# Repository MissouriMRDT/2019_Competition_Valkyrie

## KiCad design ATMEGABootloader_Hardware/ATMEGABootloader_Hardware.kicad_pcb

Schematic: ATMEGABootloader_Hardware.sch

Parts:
A1: Arduino_UNO_R3
C1, C2: 20pF; C_0603_1608Metric_Pad1.05x0.95mm_HandSolder
JP1, JP2, JP3: Jumper; PinHeader_1x02_P2.54mm_Vertical
R1: 10k; R_0603_1608Metric_Pad1.05x0.95mm_HandSolder
U1: ATmega328-PU; DIP-28_W7.62mm
Y1: 16MHz; Crystal_HC49-U_Vertical

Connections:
+5V: A1.5, JP2.2, U1.7, U1.20
GND: A1.6, A1.7, A1.29, C1.1, C2.1, U1.8, U1.22
unnamed: C1.2, JP3.2, Y1.1
unnamed: C2.2, U1.10, Y1.2
unnamed: JP1.1, U1.2
unnamed: JP2.1, R1.1
unnamed: JP3.1, U1.9
P17: A1.26, U1.17
P18: A1.27, U1.18
P19: A1.28, U1.19
Rst: A1.25, R1.2, U1.1
Rx: A1.15, JP1.2
Tx: A1.16, U1.3

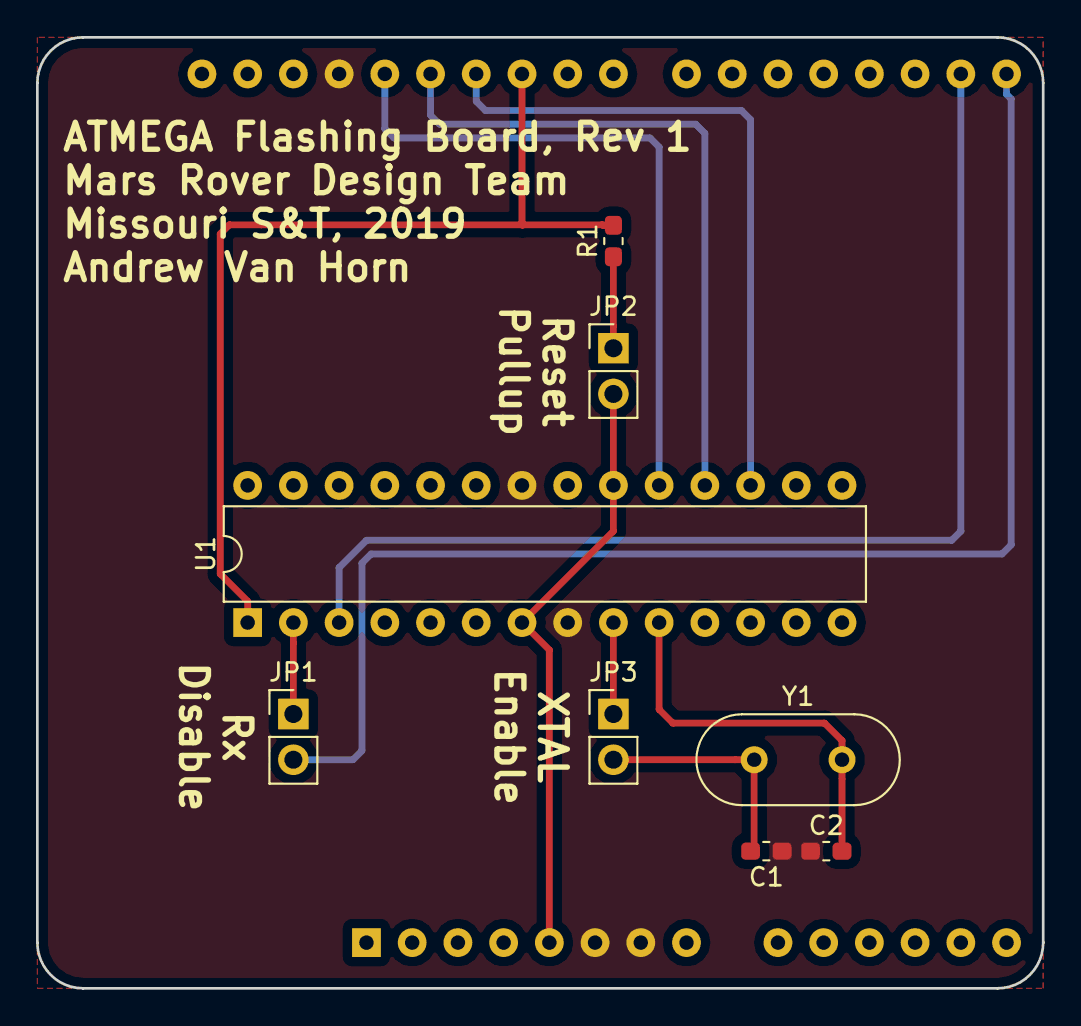
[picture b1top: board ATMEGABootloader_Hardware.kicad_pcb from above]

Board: 2 copper layers, 55.9 x 52.8 mm, 9 parts (1 on the bottom side), 13 nets.

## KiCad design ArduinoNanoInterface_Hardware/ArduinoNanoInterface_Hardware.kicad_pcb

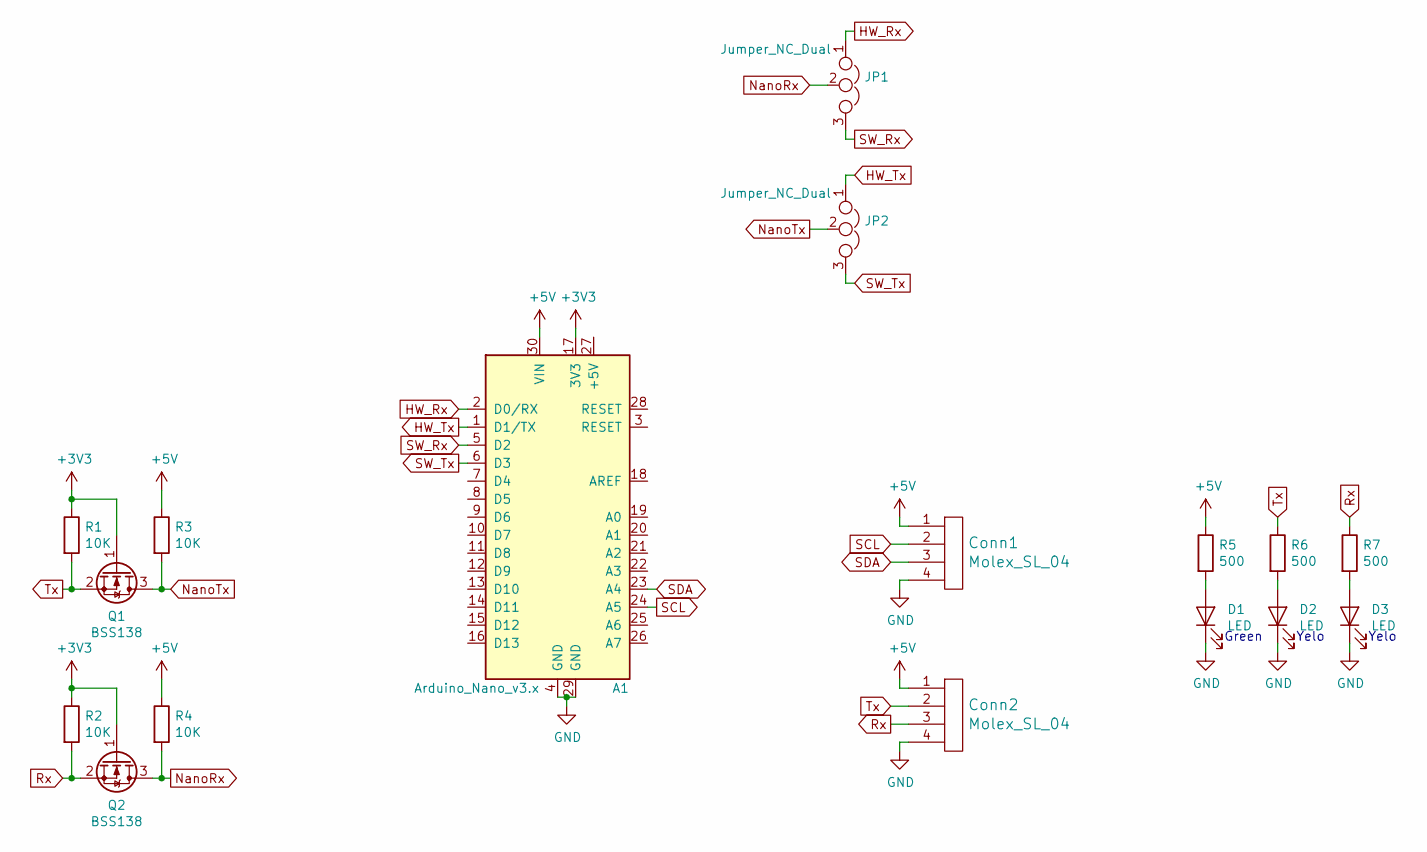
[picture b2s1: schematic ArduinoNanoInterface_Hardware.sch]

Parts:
A1: Arduino_Nano_v3.x; Arduino_Nano
Conn1, Conn2: Molex_SL_04; MOLEX_SL_04_Horizontal
D1, D2, D3: LED; LED_0603_1608Metric_Pad1.05x0.95mm_HandSolder
JP1, JP2: Jumper_NC_Dual; PinSocket_1x03_P2.54mm_Vertical
Q1, Q2: BSS138; SOT-23
R1, R2, R3, R4: 10K; R_0603_1608Metric_Pad1.05x0.95mm_HandSolder
R5, R6, R7: 500; R_0603_1608Metric_Pad1.05x0.95mm_HandSolder

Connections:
+3V3: A1.17 (3V3), Q1.1 (G), Q2.1 (G), R1.1, R2.1
+5V: A1.30 (VIN), Conn1.1, Conn2.1, R3.1, R4.1, R5.1
GND: A1.4 (GND), A1.29 (GND), Conn1.4, Conn2.4, D1.1 (K), D2.1 (K), D3.1 (K)
HW_Rx: A1.2 (D0/RX), JP1.1
HW_Tx: A1.1 (D1/TX), JP2.1
NanoRx: JP1.2, Q2.3 (D), R4.2
NanoTx: JP2.2, Q1.3 (D), R3.2
unnamed: D1.2 (A), R5.2
unnamed: D2.2 (A), R6.2
unnamed: D3.2 (A), R7.2
Rx: Conn2.3, Q2.2 (S), R2.2, R7.1
SCL: A1.24 (A5), Conn1.2
SDA: A1.23 (A4), Conn1.3
SW_Rx: A1.5 (D2), JP1.3
SW_Tx: A1.6 (D3), JP2.3
Tx: Conn2.2, Q1.2 (S), R1.2, R6.1

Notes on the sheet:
Green
Yelo

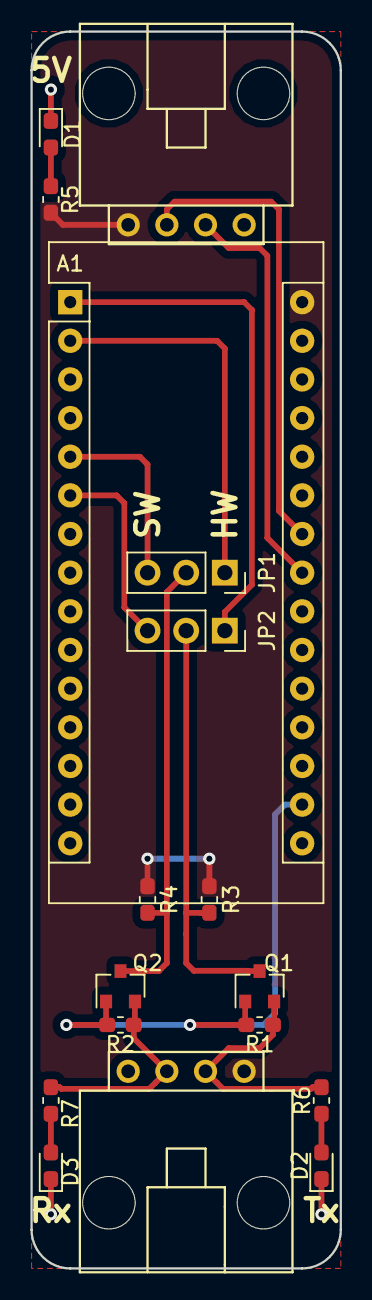
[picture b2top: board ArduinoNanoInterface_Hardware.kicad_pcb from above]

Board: 2 copper layers, 20.3 x 81.3 mm, 17 parts (0 on the bottom side), 16 nets.

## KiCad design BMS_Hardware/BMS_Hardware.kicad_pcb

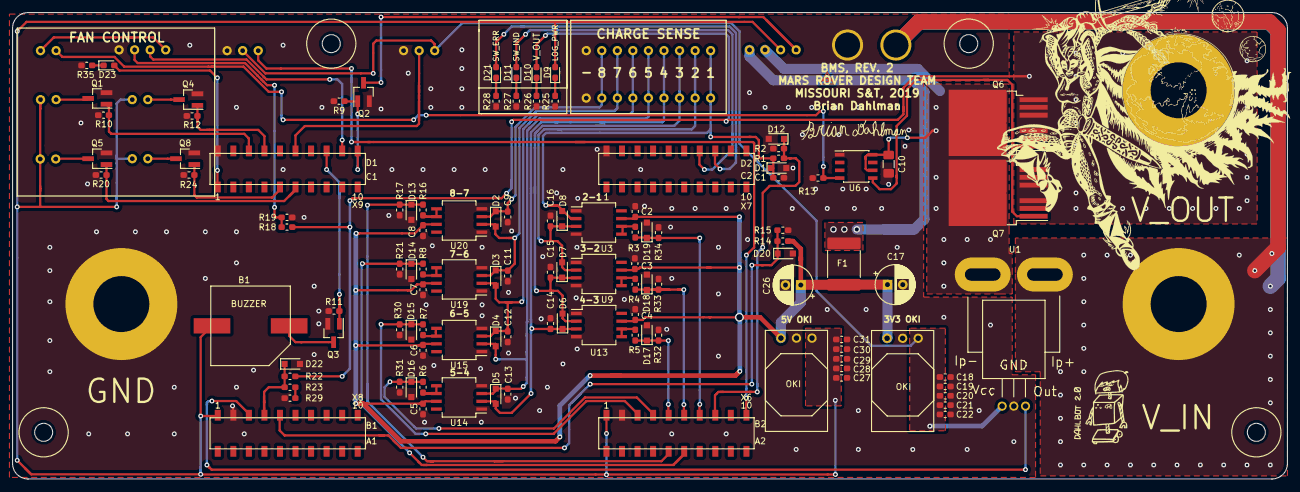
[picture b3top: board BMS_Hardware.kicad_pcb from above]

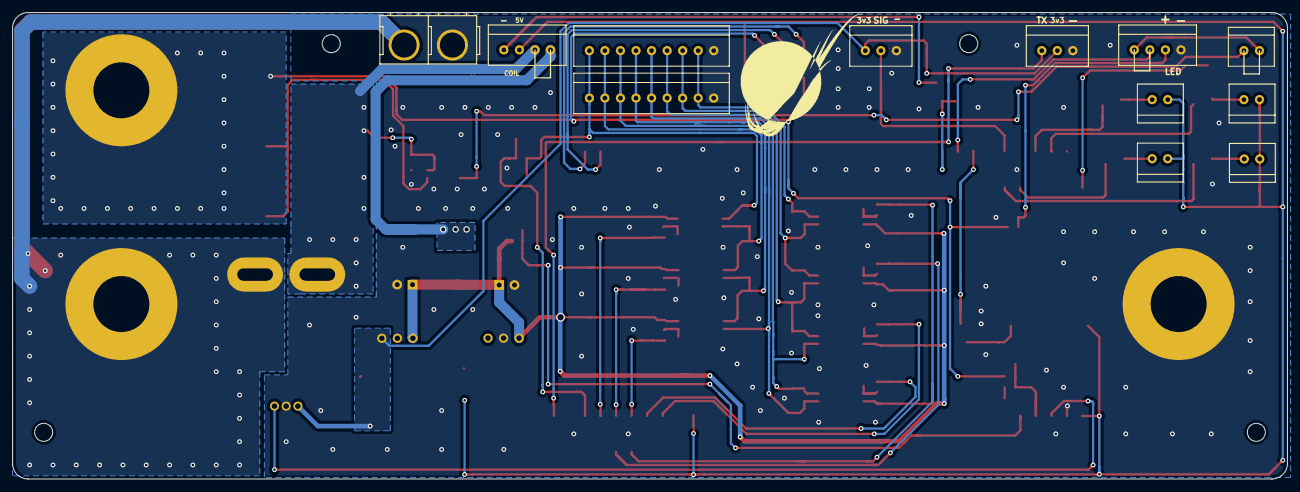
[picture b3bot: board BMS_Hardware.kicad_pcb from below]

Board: 2 copper layers, 208.3 x 76.2 mm, 123 parts (12 on the bottom side), 62 nets.

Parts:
B1: BUZZER_SMI_1324_TW_5V_2_R
C1, C2, C3, C4, C5, C6, C7, C8, C9, C11, C12, C13, C14, C15, C16: 1u; C_0603_1608Metric_Pad1.05x0.95mm_HandSolder
C10: 10u; C_1206_3216Metric_Pad1.42x1.75mm_HandSolder
C17, C26: 22u 50V; CP_Radial_D6.3mm_P2.50mm
C18, C19, C20, C21, C27, C28, C29, C30: 10u; C_0603_1608Metric_Pad1.05x0.95mm_HandSolder
C22, C31: 0.1u; C_0603_1608Metric_Pad1.05x0.95mm_HandSolder
Conn1: CHARGE_SENSE_BOTTOM; MOLEX_SL_09_Vertical
Conn2: CHARGE_SENSE_TOP; MOLEX_SL_09_Vertical
Conn3: AndersonPP; Anderson_2_Vertical_Sidy_by_Side
D1, D2, D3, D4, D5, D6, D7, D8: 7.5V; D_SOD-323_HandSoldering
D9: LOG_PWR_LED; LED_0603_1608Metric_Pad1.05x0.95mm_HandSolder
D10: PACK_V_IND_LED_ORANGE; LED_0603_1608Metric_Pad1.05x0.95mm_HandSolder
D11: SW_IND_LED_BLUE; LED_0603_1608Metric_Pad1.05x0.95mm_HandSolder
D12, D13, D14, D15, D16, D17, D18, D19, D20, D22: D_Zener; D_SOD-323_HandSoldering
D21: SW_ERR_LED_RED; LED_0603_1608Metric_Pad1.05x0.95mm_HandSolder
D23: FAN_PWR_LED_ORANGE; LED_0603_1608Metric_Pad1.05x0.95mm_HandSolder
F1: PTC2920; Fuse_2920_7451Metric
Q1, Q2, Q3, Q4, Q5, Q8: 2N7002PW; SOT-23_Handsoldering
Q6, Q7: IRLS3034-7P; IRLS3034_TO-263-7_P
R1, R3, R4, R5, R6, R7, R8, R9, R13, R16, R19, R23: 10k; R_0603_1608Metric_Pad1.05x0.95mm_HandSolder
R2, R17, R21, R30, R31, R32, R33, R34: 36.5k; R_0603_1608Metric_Pad1.05x0.95mm_HandSolder
R10, R12, R20, R24: 100K; R_0603_1608Metric_Pad1.05x0.95mm_HandSolder
R11: 10K; R_0603_1608Metric_Pad1.05x0.95mm_HandSolder
R14: 1M; R_0603_1608Metric_Pad1.05x0.95mm_HandSolder
R15, R22: 100k; R_0603_1608Metric_Pad1.05x0.95mm_HandSolder
R18: 4k; R_0603_1608Metric_Pad1.05x0.95mm_HandSolder
R25, R27, R28, R35: 500; R_0603_1608Metric_Pad1.05x0.95mm_HandSolder
R26: 1.5k; R_0603_1608Metric_Pad1.05x0.95mm_HandSolder
R29: 820; R_0603_1608Metric_Pad1.05x0.95mm_HandSolder
U1: ACS759ECB-200B-PFF-T; ACS759ECB_PFF_Leadform_5pins
U2: FAN_1; MOLEX_SL_02_Vertical
U3, U9, U13, U14, U15, U19, U20: INA132; SO-8_5.3x6.2mm_P1.27mm
U4: FAN_2; MOLEX_SL_02_Vertical
U5: BMS_Logic_Switch; MOLEX_SL_04_Vertical
U6: LT1910; SOIC-8_3.9x4.9mm_Pitch1.27mm
U7: E_STOP; MOLEX_SL_02_Vertical
U8: FAN_3; MOLEX_SL_02_Vertical
U10: E_STOP+LED; MOLEX_SL_04_Vertical
U11: TEMP_1; MOLEX_SL_03_Vertical
U12: FAN_4; MOLEX_SL_02_Vertical
U16, U18: OKI; OKI_Horizontal
U17: Indicator Comm; MOLEX_SL_03_Vertical
U21: TM4C129E_Launchpad; TM4C129E_Launchpad_FULL_SMD_TOP
V1, V2, V3: BATT_PWR_VIA

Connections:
+3V3: C18.1, C19.1, C20.1, C21.1, C22.1, U1.1, U11.1, U16.3, U17.2
+5V: B1.1, C27.1, C28.1, C29.1, C30.1, C31.1, D9.2, U2.1, U4.1, U5.2, U8.1, U12.1, U18.3, U21.+5V, U21.+5V'
/V_IN: Conn3.2, U1.4, V2.1
BUZZER: Q3.1, R11.2, U21.PN2
CELL_1: C1.2, Conn1.1, Conn2.1, D1.1, D8.2, R1.2, U3.2
CELL_1-GND_SENSE: D12.1, R1.1, R2.1, U21.PK3
CELL_2: C16.1, Conn1.2, Conn2.2, D7.2, D8.1, U3.3, U9.2
CELL_2-1_SENSE: D19.1, R3.1, R34.1, U21.PK2
CELL_3: C15.1, Conn1.3, Conn2.3, D6.2, D7.1, U9.3, U13.2
CELL_3-2_SENSE: D18.1, R4.1, R33.1, U21.PK1
CELL_4: C14.1, Conn1.4, Conn2.4, D5.2, D6.1, U13.3, U14.2
CELL_4-3_SENSE: D17.1, R5.1, R32.1, U21.PK0
CELL_5: C13.1, Conn1.5, Conn2.5, D4.2, D5.1, U14.3, U15.2
CELL_5-4_SENSE: D16.1, R6.1, R31.1, U21.PB5
CELL_6: C12.1, Conn1.6, Conn2.6, D3.2, D4.1, U15.3, U19.2
CELL_6-5_SENSE: D15.1, R7.1, R30.1, U21.PB4
CELL_7: C11.2, Conn1.7, Conn2.7, D2.2, D3.1, U19.3, U20.2
CELL_7-6_SENSE: D14.1, R8.1, R21.1, U21.PD5
CELL_8: C9.1, Conn1.8, Conn2.8, D2.1, U20.3
CELL_8-7_SENSE: D13.1, R16.1, R17.1, U21.PD4
E-Stop_Gate: Q6.1, Q7.1, U6.5
FAN_CTL_1: Q1.1, R10.2, U21.PH2
FAN_CTL_2: Q4.1, R12.2, U21.PH3
FAN_CTL_3: Q5.1, R20.2, U21.PL5
FAN_CTL_4: Q8.1, R24.2, U21.PL4
FAN_PWR: D23.2, U21.PF1
GND: C1.1, C2.1, C3.1, C4.1, C5.1, C6.1, C7.1, C8.2, C9.2, C10.2, C11.1, C12.2, C13.2, C14.2, C15.2, C16.2, C17.2, C18.2, C19.2, C20.2, C21.2, C22.2, C26.2, C27.2, C28.2, C29.2, C30.2, C31.2, Conn1.9, Conn2.9, Conn3.1, D1.2, D12.2, D13.2, D14.2, D15.2, D16.2, D17.2, D18.2, D19.2, D20.2, D22.2, Q1.2, Q2.2, Q3.2, Q4.2, Q5.2, Q8.2, R2.2, R9.2, R10.1, R11.1, R12.1, R13.2, R15.2, R17.2, R19.2, R20.1, R21.2, R24.1, R25.2, R26.2, R27.2, R28.2, R29.2, R30.2, R31.2, R32.2, R33.2, R34.2, R35.2, U1.2, U3.1, U3.4, U6.1, U9.1, U9.4, U10.4, U11.3, U13.1, U13.4, U14.1, U14.4, U15.1, U15.4, U16.2, U17.3, U18.2, U19.1, U19.4, U20.1, U20.4, U21.GND, V1.1
LOGIC_PWR: C2.2, C3.2, C4.2, C5.2, C6.2, C7.2, C8.1, C17.1, C26.1, F1.1, R14.1, U3.7, U9.7, U13.7, U14.7, U15.7, U16.1, U18.1, U19.7, U20.7
LOGIC_SWITCH: Q2.1, R9.1, U21.PP2
unnamed: B1.2, Q3.3
unnamed: C10.1, Q6.2, Q7.2, U1.5, U5.3, U6.6, U6.8
unnamed: D9.1, R25.1
unnamed: D10.1, R26.1
unnamed: D11.1, R27.1
unnamed: D21.1, R28.1
unnamed: D23.1, R35.1
unnamed: F1.2, U5.4
unnamed: Q1.3, U2.2
unnamed: Q2.3, U5.1
unnamed: Q4.3, U4.2
unnamed: Q5.3, U8.2
unnamed: Q8.3, U12.2
unnamed: R3.2, U3.5, U3.6
unnamed: R4.2, U9.5, U9.6
unnamed: R5.2, U13.5, U13.6
unnamed: R6.2, U14.5, U14.6
unnamed: R7.2, U15.5, U15.6
unnamed: R8.2, U19.5, U19.6
unnamed: R13.1, U6.4, U7.1
unnamed: R16.2, U20.5, U20.6
unnamed: R18.1, R19.1, U10.3
unnamed: R23.1, R29.1
unnamed: U7.2, U10.1
PACK_GATE: U10.2, U21.PN3
PACK_I_SENSE: U1.3, U21.PE0
SER_TX_IND: U17.1, U21.PA5
SW_ERR: D21.2, U21.PP3
SW_IND: D11.2, U21.PQ3
TEMP_D_OUT: U11.2, U21.PD1
V_LOG_SENSE: D20.1, R14.2, R15.1, U21.PE2
V_OUT: D10.2, Q6.3, Q7.3, R18.2, R22.1, V3.1
V_OUT_SENSE: D22.1, R22.2, R23.2, U21.PE1

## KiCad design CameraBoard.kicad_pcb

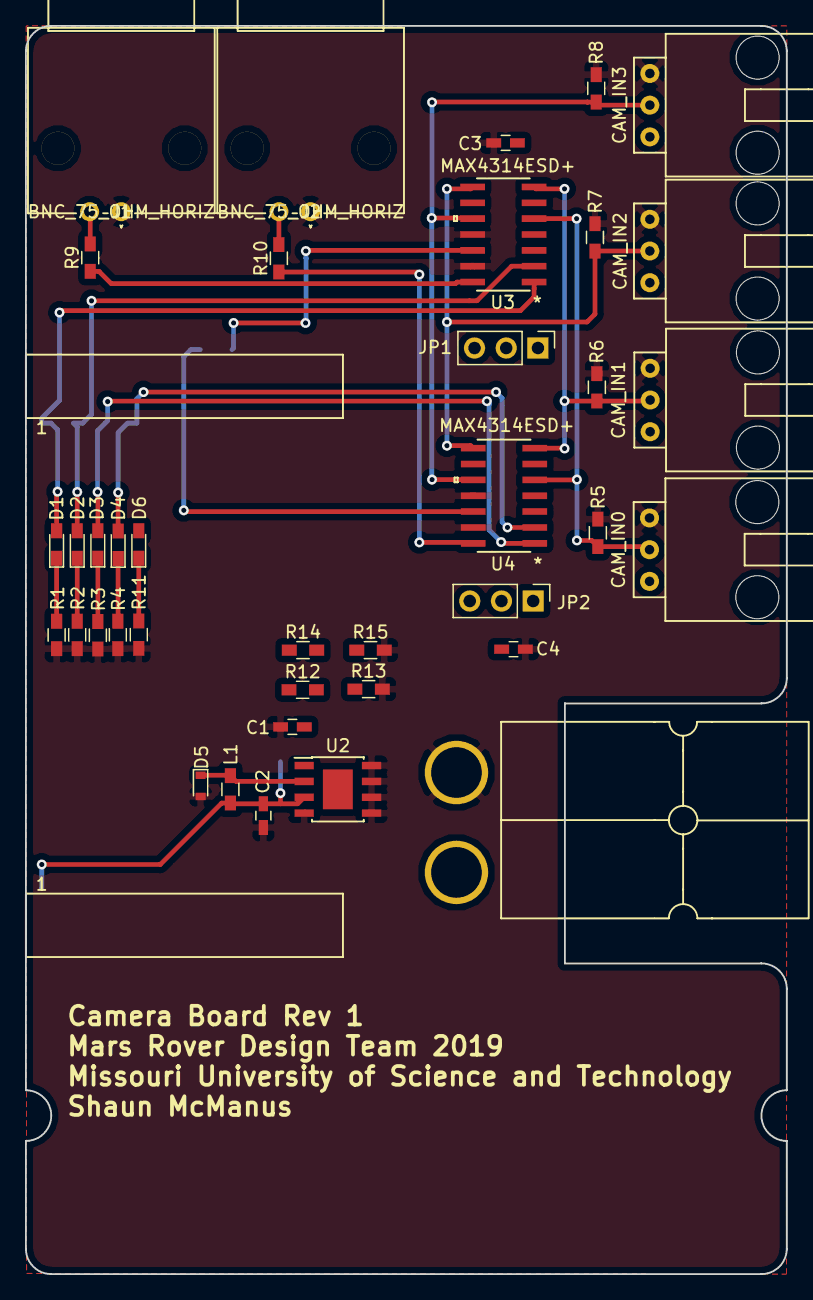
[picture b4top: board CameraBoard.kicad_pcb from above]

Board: 2 copper layers, 61.0 x 100.0 mm, 39 parts (0 on the bottom side), 28 nets.

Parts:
C1, C2, C3, C4: 10u; C_0603_HandSoldering
CAM_IN0: CAM_0; MOLEX_SL_03_Horizontal
CAM_IN1: CAM_1; MOLEX_SL_03_Horizontal
CAM_IN2: CAM_2; MOLEX_SL_03_Horizontal
CAM_IN3: CAM_3; MOLEX_SL_03_Horizontal
Conn1: AndersonPP; Anderson_2_Horisontal_Side_by_Side
D1, D2, D3, D4, D6: LED; LED_0603_HandSoldering
D5: D_Schottky; D_0603
J1, J2: BNC_75_OHM_HORIZ; BNC-75-Ohm-HORIZONTAL-1-1478032-0
JP1, JP2: Jumper_NC_Dual; Pin_Header_Straight_1x03_Pitch2.54mm
L1: 47u; L_0603_HandSoldering
R1, R2, R3, R4, R11, R13, R15: 500; R_0603_HandSoldering
R5, R6, R7, R8, R9, R10: 75; R_0603_HandSoldering
R12, R14: 100; R_0603_HandSoldering
U1: TM4C129E_Launchpad; TM4C129E_Launchpad_X9_SMD
U2: AP1059; HTSOP-8-1EP_3.9x4.9mm_Pitch1.27mm
U3, U4: MAX4314ESD+; MAX4314ESD&plus_

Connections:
+5V: C2.2, JP1.3, JP2.3, L1.2, U1.+5V, U2.3
+12V: C1.1, CAM_IN0.3, CAM_IN1.3, CAM_IN2.3, CAM_IN3.3, Conn1.2, R12.1, R14.1, U2.1
CAM_IN0: CAM_IN0.2, R5.2, U3.5, U4.5
CAM_IN1: CAM_IN1.2, R6.2, U3.7, U4.7
CAM_IN2: CAM_IN2.2, R7.2, U3.8, U4.8
CAM_IN3: CAM_IN3.2, R8.2, U3.10, U4.10
CAM_OUT0: R9.1, U3.14
CAM_OUT1: R10.1, U4.14
GND: C1.2, C2.1, C3.2, C4.2, CAM_IN0.1, CAM_IN1.1, CAM_IN2.1, CAM_IN3.1, Conn1.1, D5.2, J1.1, J2.1, R1.2, R2.2, R3.2, R4.2, R5.1, R6.1, R7.1, R8.1, R11.2, R13.2, R15.2, U1.GND, U2.4, U2.5, U2.6, U2.7, U2.8, U3.11, U3.13, U4.11, U4.13
MUXA0: D2.2, U1.PF2, U3.2
MUXA1: D1.2, U1.PF1, U3.1
MUXA_SHDN: U1.PD0, U3.12
MUXB0: D4.2, U1.PG0, U4.2
MUXB1: D3.2, U1.PF3, U4.1
MUXB_SHDN: U1.PD1, U4.12
unnamed: C3.1, JP1.2, U3.4
unnamed: C4.1, JP2.2, U4.4
unnamed: D1.1, R1.1
unnamed: D2.1, R2.1
unnamed: D3.1, R3.1
unnamed: D4.1, R4.1
unnamed: D5.1, L1.1, U2.2
unnamed: D6.1, R11.1
unnamed: J1.2, R9.2
unnamed: J2.2, R10.2
unnamed: JP1.1, R14.2, R15.1
unnamed: JP2.1, R12.2, R13.1
SW_ERR: D6.2, U1.PP2

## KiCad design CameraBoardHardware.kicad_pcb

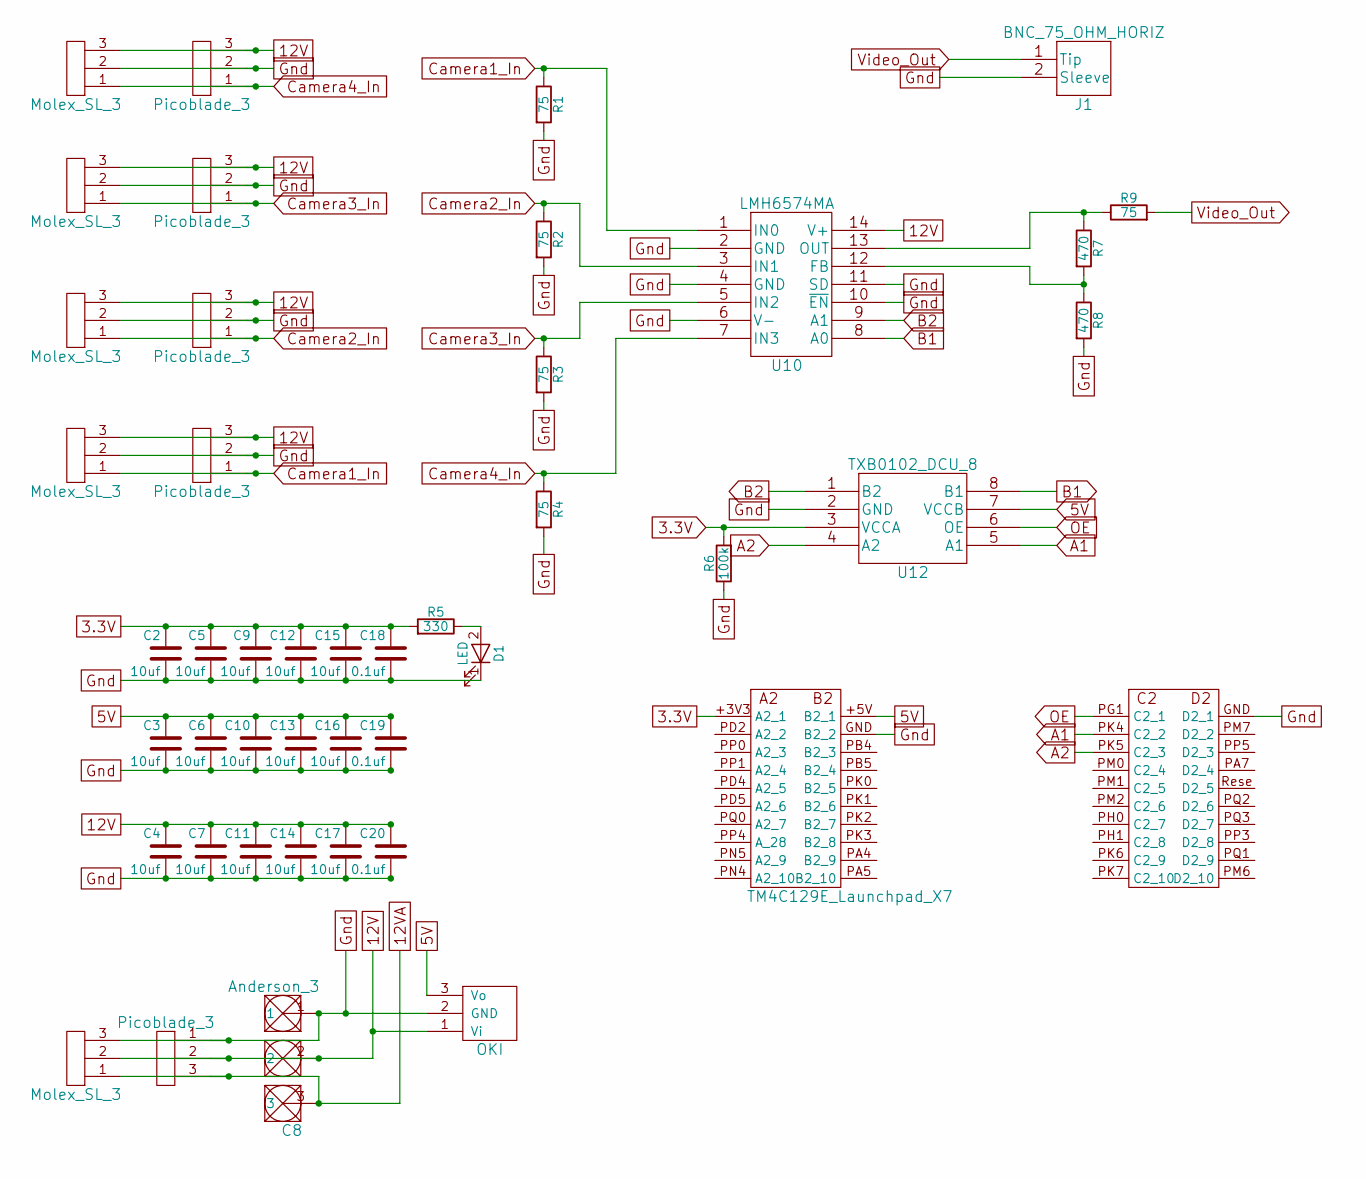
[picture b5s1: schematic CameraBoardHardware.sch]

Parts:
C2, C3, C4, C5, C6, C7, C9, C10, C11, C12, C13, C14, C15, C16, C17: 10uf; C_0603_HandSoldering
C8: Anderson_3; Anderson_3_Horisontal_Side_by_Side
C18, C19, C20: 0.1uf; C_0603_HandSoldering
D1: LED; LED_0603_HandSoldering
J1: BNC_75_OHM_HORIZ; BNC-75-Ohm-HORIZONTAL-1-1478032-0
R1, R2, R3, R4, R9: 75; R_0603_HandSoldering
R5: 330; R_0603_HandSoldering
R6: 100k; R_0603_HandSoldering
R7, R8: 470; R_0603_HandSoldering
U1, U2, U3, U4, U14: Picoblade_3; Molex_PicoBlade_53047-0310_03x1.25mm_Straight
U5, U6, U7, U8, U13: Molex_SL_3; MOLEX_SL_3_Horizontal
U9: OKI; OKI_Horisontal
U10: LMH6574MA; LMH6574MA&slash_NOPB
U11: TM4C129E_Launchpad_X7; TM4C129E_Launchpad_X7_Bottom_SMD
U12: TXB0102_DCU_8; TXB0102DCUR

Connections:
3.3V: C2.1, C5.1, C9.1, C12.1, C15.1, C18.1, R5.2, R6.2, U11.+3V3 (A2_1), U12.3 (VCCA)
5V: C3.1, C6.1, C10.1, C13.1, C16.1, C19.1, U9.3 (Vo), U11.+5V (B2_1), U12.7 (VCCB)
12V: C4.1, C7.1, C8.2, C11.1, C14.1, C17.1, C20.1, U1.3, U2.3, U3.3, U4.3, U5.3, U6.3, U7.3, U8.3, U9.1 (Vi), U10.14 (V+), U13.2, U14.2
12VA: C8.3, U13.1, U14.3
A1: U11.PK4 (C2_2), U12.5 (A1)
A2: U11.PK5 (C2_3), U12.4 (A2)
B1: U10.8 (A0), U12.8 (B1)
B2: U10.9 (A1), U12.1 (B2)
Camera1_In: R1.1, U4.1, U8.1, U10.1 (IN0)
Camera2_In: R2.1, U3.1, U7.1, U10.3 (IN1)
Camera3_In: R3.1, U2.1, U6.1, U10.5 (IN2)
Camera4_In: R4.1, U1.1, U5.1, U10.7 (IN3)
Gnd: C2.2, C3.2, C4.2, C5.2, C6.2, C7.2, C8.1, C9.2, C10.2, C11.2, C12.2, C13.2, C14.2, C15.2, C16.2, C17.2, C18.2, C19.2, C20.2, D1.1 (K), J1.2 (Sleeve), R1.2, R2.2, R3.2, R4.2, R6.1, R8.2, U1.2, U2.2, U3.2, U4.2, U5.2, U6.2, U7.2, U8.2, U9.2 (GND), U10.2 (GND), U10.4 (GND), U10.6 (V-), U10.10 (~EN), U10.11 (SD), U11.GND (B2_2), U12.2 (GND), U13.3, U14.1
unnamed: D1.2 (A), R5.1
unnamed: R7.1, R9.1, U10.13 (OUT)
unnamed: R7.2, R8.1, U10.12 (FB)
OE: U11.PG1 (C2_1), U12.6 (OE)
Video_Out: J1.1 (Tip), R9.2

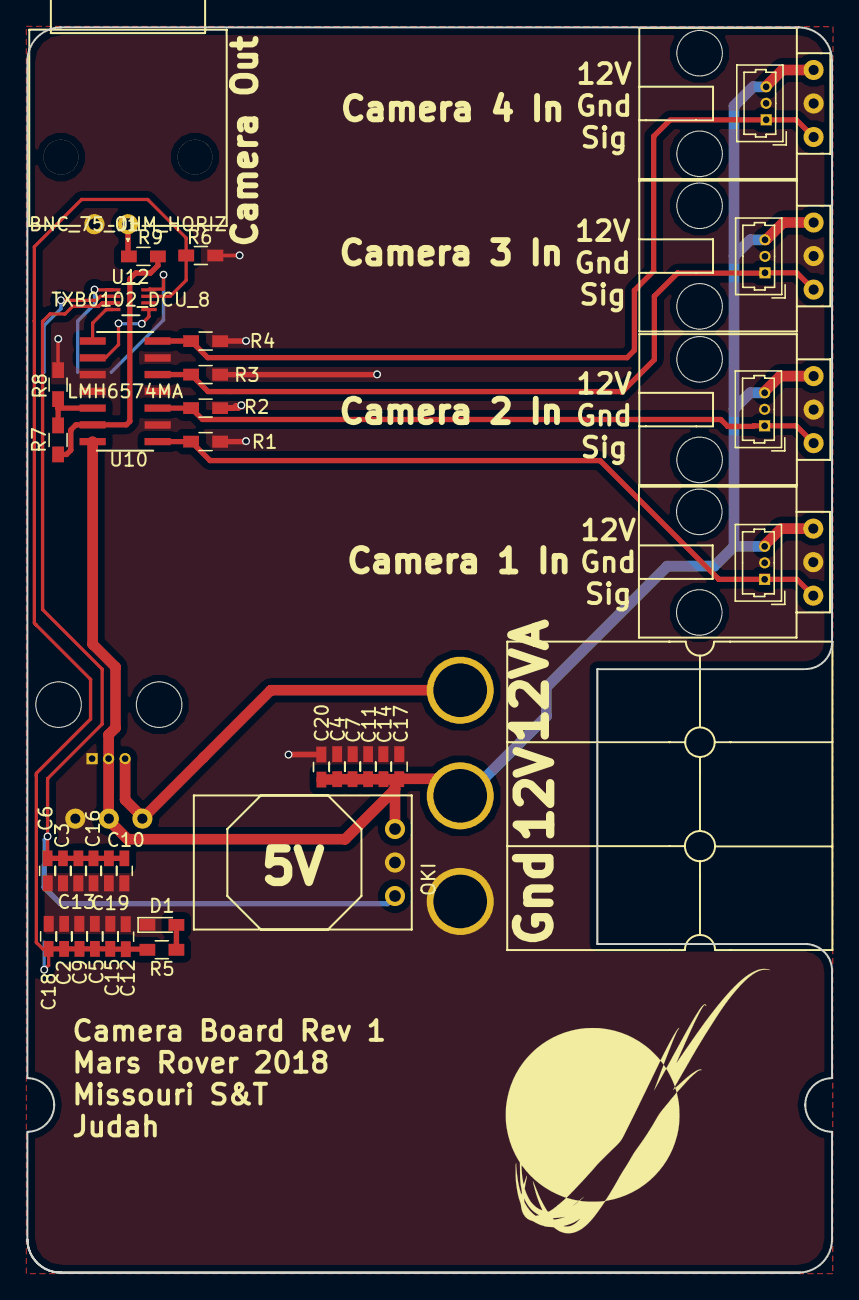
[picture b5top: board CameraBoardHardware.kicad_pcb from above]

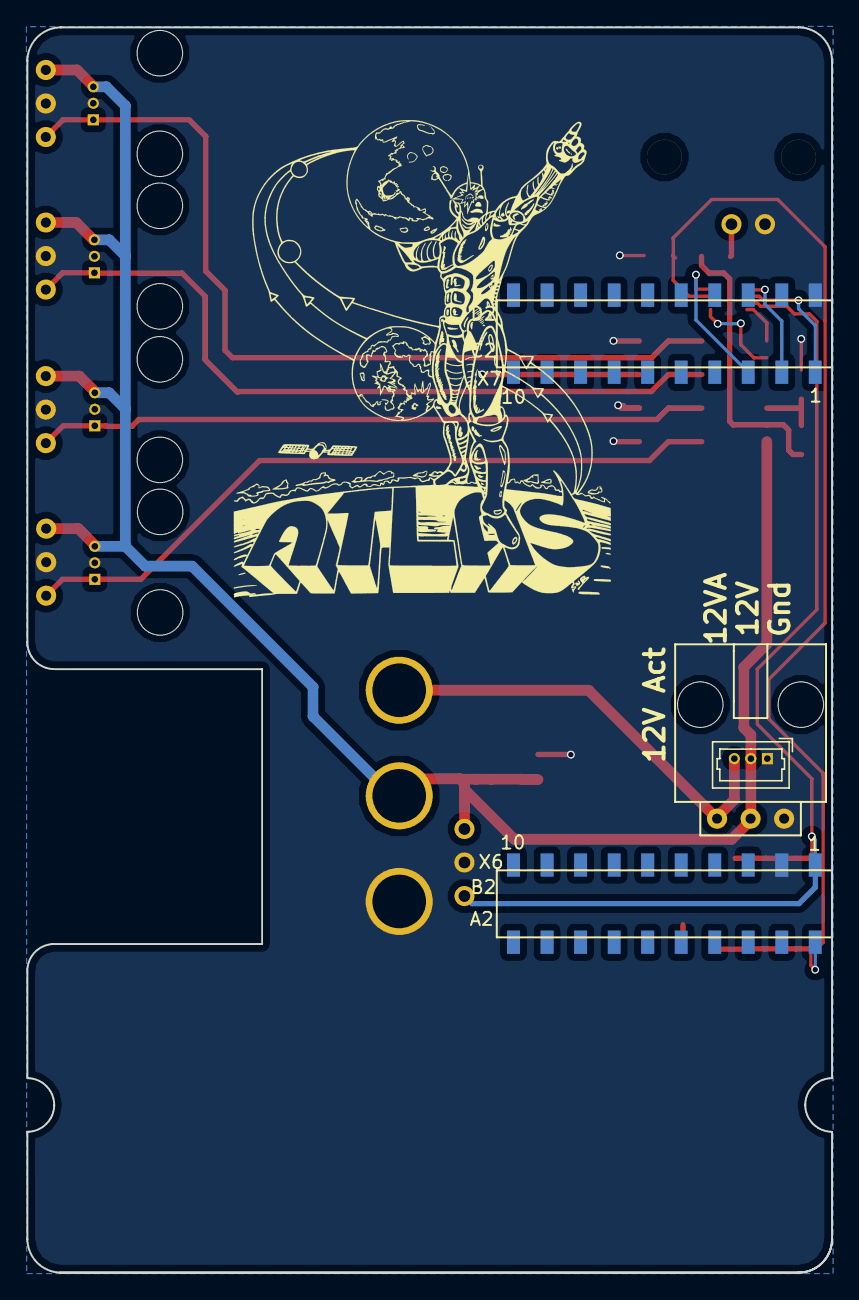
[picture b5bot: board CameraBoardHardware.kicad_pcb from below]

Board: 2 copper layers, 61.0 x 94.3 mm, 44 parts (2 on the bottom side), 18 nets.

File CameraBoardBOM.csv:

"Id","Designator","Package","Quantity","Designation","Supplier and ref",
1,"C8","Anderson_3_Horisontal_Side_by_Side",1,"Anderson_3",,,
2,"U9","OKI_Horisontal",1,"OKI",,,
3,"U13","MOLEX_SL_3_Horizontal",1,"Molex_SL_3",,,
4,"U14","Molex_PicoBlade_53047-0310_03x1.25mm_Straight",1,"Picoblade_3",,,
5,"C2,C3,C4,C5,C6,C7,C9,C10,C11,C12,C13,C14,C15,C16,C17","C_0603_HandSoldering",15,"10uf",,,
6,"C18,C19,C20","C_0603_HandSoldering",3,"0.1uf",,,
7,"D1","LED_0603_HandSoldering",1,"LED",,,
8,"J1","BNC-75-Ohm-HORIZONTAL-1-1478032-0",1,"BNC_75_OHM_HORIZ",,,
9,"R1,R2,R3,R4,R9","R_0603_HandSoldering",5,"75",,,
10,"R5","R_0603_HandSoldering",1,"330",,,
11,"R6","R_0603_HandSoldering",1,"100k",,,
12,"R7,R8","R_0603_HandSoldering",2,"470",,,
13,"U10","LMH6574MA&slash_NOPB",1,"LMH6574MA",,,
14,"U12","TXB0102DCUR",1,"TXB0102_DCU_8",,,
15,"U11","TM4C129E_Launchpad_X7_Bottom_SMD",1,"TM4C129E_Launchpad_X7",,,
16,"G***","Atlas_Logo_28.6mmX37.3mm",1,"LOGO",,,
17,"G***","MRDT_Logo_20mm",1,"LOGO",,,
18,"J2,J3,J4,J5","bnc-ci",4,"BNC_75_OHM_HORIZ",,,
19,"U5,U6,U7,U8","MOLEX_SL_3_Vertical",4,"Molex_SL_3",,,

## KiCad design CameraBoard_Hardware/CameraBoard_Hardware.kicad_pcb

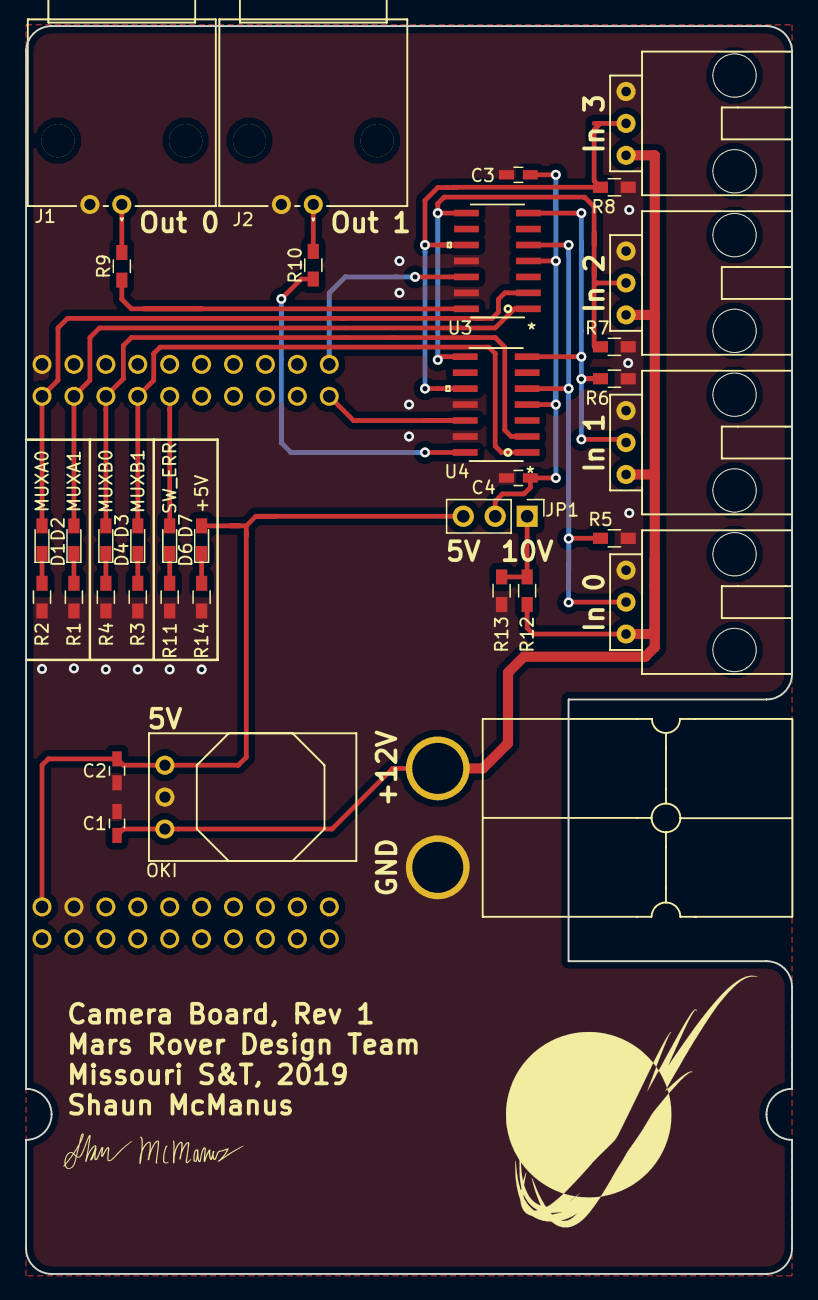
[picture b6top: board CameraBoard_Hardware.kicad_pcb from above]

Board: 2 copper layers, 61.0 x 99.3 mm, 36 parts (0 on the bottom side), 26 nets.

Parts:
C1, C2: 10uF; C_0603_HandSoldering
C3, C4: 10u; C_0603_HandSoldering
Conn1: AndersonPP; Anderson_2_Horizontal_Side_by_Side
Conn3: CAM_0; MOLEX_SL_03_Horizontal
Conn4: CAM_1; MOLEX_SL_03_Horizontal
Conn5: CAM_2; MOLEX_SL_03_Horizontal
Conn6: CAM_3; MOLEX_SL_03_Horizontal
D1, D2, D3, D4, D6, D7: LED; LED_0603_HandSoldering
J1, J2: BNC_75_OHM_HORIZ; BNC_THT_Horizontal
JP1: Jumper_NC_Dual; Pin_Header_Straight_1x03_Pitch2.54mm
R1, R2, R3, R4, R11, R13, R14: 500; R_0603_HandSoldering
R5, R6, R7, R8, R9, R10: 75; R_0603_HandSoldering
R12: 100; R_0603_HandSoldering
U1: TM4C129E_Launchpad; TM4C129E_Launchpad_X9_THT_BOTTOM
U2: OKI; OKI_Horizontal
U3, U4: MAX4314ESD+

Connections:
+5V: C2.1, D7.2, JP1.3, U1.+5V, U2.3
+10V: JP1.1, R12.2, R13.1
+12V: C1.1, Conn1.2, Conn3.3, Conn4.3, Conn5.3, Conn6.3, R12.1, U2.1
/MUX_PWR: C3.1, C4.1, JP1.2, U3.4, U4.4
CAM_IN0: Conn3.2, R5.2, U3.5, U4.5
CAM_IN1: Conn4.2, R6.2, U3.7, U4.7
CAM_IN2: Conn5.2, R7.2, U3.8, U4.8
CAM_IN3: Conn6.2, R8.2, U3.10, U4.10
CAM_OUT0: R9.1, U3.14
CAM_OUT1: R10.1, U4.14
GND: C1.2, C2.2, C3.2, C4.2, Conn1.1, Conn3.1, Conn4.1, Conn5.1, Conn6.1, J1.2, J2.2, R1.2, R2.2, R3.2, R4.2, R5.1, R6.1, R7.1, R8.1, R11.2, R13.2, R14.2, U1.GND, U2.2, U3.11, U3.13, U4.11, U4.13
MUXA0: D2.2, U1.PF1, U3.2
MUXA1: D1.2, U1.PF2, U3.1
MUXA_SHDN: U1.PP2, U3.12
MUXB0: D4.2, U1.PF3, U4.2
MUXB1: D3.2, U1.PG0, U4.1
MUXB_SHDN: U1.PL3, U4.12
unnamed: D1.1, R1.1
unnamed: D2.1, R2.1
unnamed: D3.1, R3.1
unnamed: D4.1, R4.1
unnamed: D6.1, R11.1
unnamed: D7.1, R14.1
unnamed: J1.1, R9.2
unnamed: J2.1, R10.2
SW_ERR: D6.2, U1.PL4

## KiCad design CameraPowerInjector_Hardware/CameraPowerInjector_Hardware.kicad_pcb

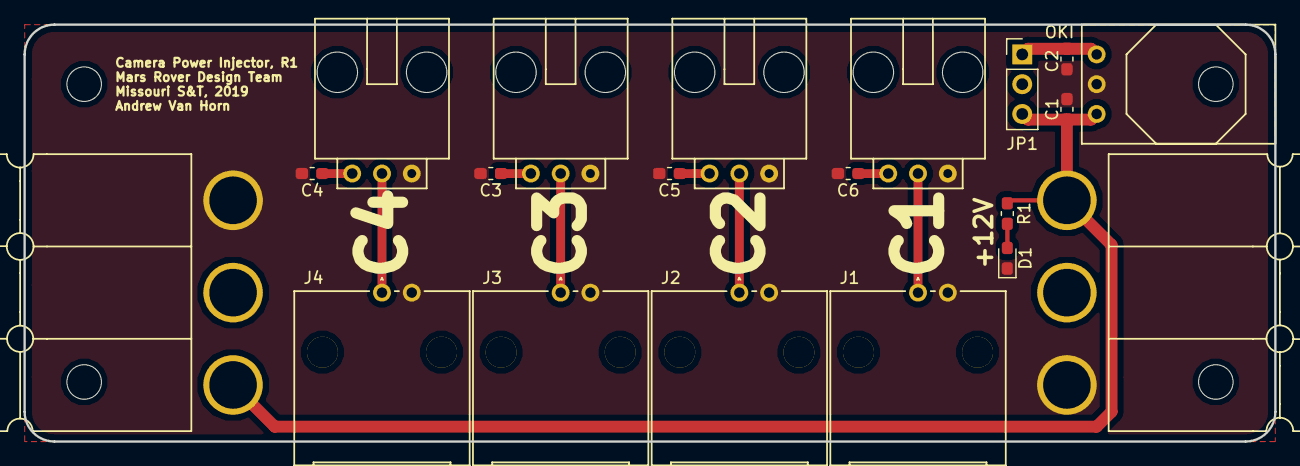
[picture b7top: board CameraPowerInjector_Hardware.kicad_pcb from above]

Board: 2 copper layers, 106.7 x 35.6 mm, 20 parts (0 on the bottom side), 9 nets.

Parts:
C1, C2, C3, C4, C5, C6: 10u; C_0603_1608Metric_Pad1.05x0.95mm_HandSolder
Conn1, Conn6: AndersonPP; Anderson_3_Horizontal_Side_by_Side
Conn2, Conn3, Conn4, Conn5: Molex_SL_03; MOLEX_SL_03_Horizontal
D1: LED; LED_0603_1608Metric_Pad1.05x0.95mm_HandSolder
J1, J2, J3, J4: Conn_Coaxial; BNC_THT_Horizontal
JP1: Jumper_NC_Dual; PinHeader_1x03_P2.54mm_Vertical
R1: 1.5K; R_0603_1608Metric_Pad1.05x0.95mm_HandSolder
U1: OKI; OKI_Horizontal

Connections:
C1_Sig: Conn2.2, J1.1
C2_Sig: Conn3.2, J2.1
C3_Sig: Conn4.2, J3.1
C4_Sig: Conn5.2, J4.1
GND: C1.2, C2.2, C3.2, C4.2, C5.2, C6.2, Conn1.1, Conn2.3, Conn3.3, Conn4.3, Conn5.3, Conn6.1, D1.1, J1.2, J2.2, J3.2, J4.2, U1.2
unnamed: D1.2, R1.2
VCOM: C3.1, C4.1, C5.1, C6.1, Conn2.1, Conn3.1, Conn4.1, Conn5.1, JP1.2
VDDA: C1.1, Conn1.3, Conn6.3, JP1.3, R1.1, U1.1
VDDF: C2.1, JP1.1, U1.3

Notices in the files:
parts and their libraries:
Copyright 2016 Accelerated Designs. All rights reserved.
